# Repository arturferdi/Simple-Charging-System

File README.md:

# Simple-Charging-System
A super simple charging sistem using MCP73831

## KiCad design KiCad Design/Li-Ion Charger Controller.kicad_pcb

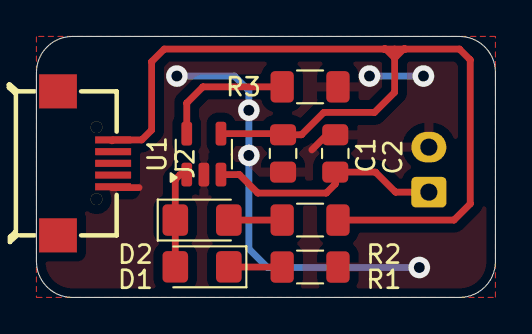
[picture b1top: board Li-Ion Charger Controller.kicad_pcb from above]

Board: 2 copper layers, 25.5 x 14.5 mm, 10 parts (1 on the bottom side), 7 nets.

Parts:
C1, C2: 4.7uF; C_0805_2012Metric_Pad1.18x1.45mm_HandSolder
D1, D2: LED; LED_1206_3216Metric_Pad1.42x1.75mm_HandSolder
J1: Conn_01x02_Socket; JST_XA_B02B-XASK-1_1x02_P2.50mm_Vertical
J2: USB_B_Micro; MICRO-USB_MICRO-USB-32
R1, R2: 390R; R_1206_3216Metric_Pad1.30x1.75mm_HandSolder
R3: 2K; R_1206_3216Metric_Pad1.30x1.75mm_HandSolder
U1: MCP73831-2-OT; SOT-23-5

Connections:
GND: C1.2, C2.2, J1.2, J2.5 (GND), R1.2, R3.2, U1.2 (V_{SS})
unnamed: D1.2 (A), D2.1 (K), U1.1 (STAT)
unnamed: D1.1 (K), R1.1
unnamed: D2.2 (A), R2.1
unnamed: C2.1, J1.1, U1.3 (V_{BAT})
unnamed: R3.1, U1.5 (PROG)
VBUS: C1.1, J2.1 (VBUS), R2.2, U1.4 (V_{DD})

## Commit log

2025-07-12 add files
